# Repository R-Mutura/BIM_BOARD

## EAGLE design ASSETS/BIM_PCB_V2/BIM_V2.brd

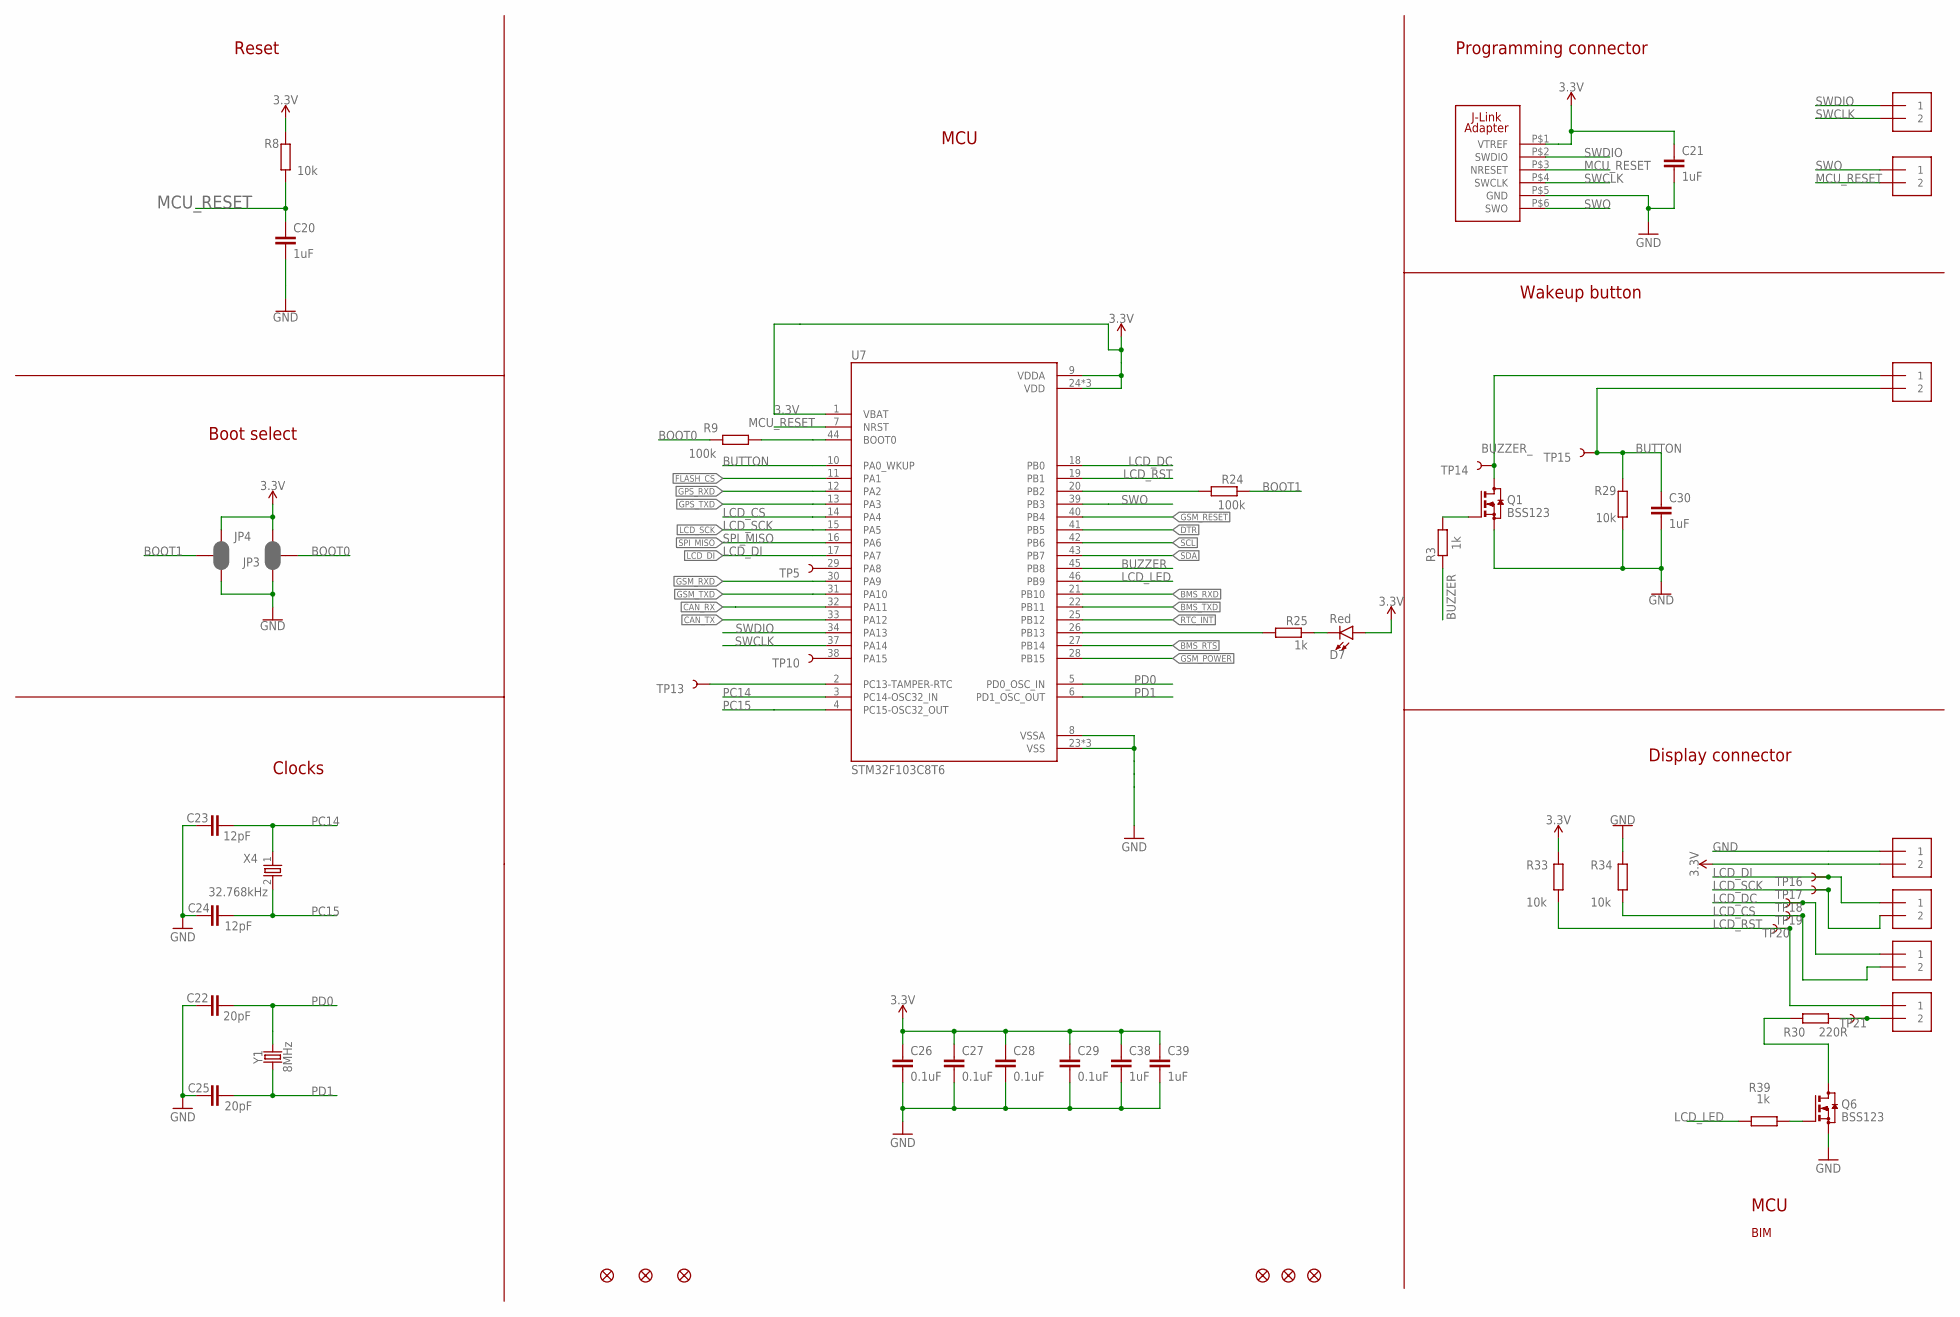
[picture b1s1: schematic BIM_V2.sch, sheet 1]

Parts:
C20, C21, C30, C38, C39: 1uF; C0402
C22, C25: 20pF; C0402
C23, C24: 12pF; C0402
C26, C27, C28, C29: 0.1uF; C0402
D7: Red; LED-0603
FD1, FD2, FD3, FD4, FD5, FD6: FIDUCIAL1X2; FIDUCIAL-1X2
JP3, JP4: JUMPER-SMT_3_2-NC_PASTE_SILK; SMT-JUMPER_3_2-NC_PASTE_SILK
Q1, Q6: BSS123; SOT23
R3, R25, R39: 1k; R0402
R8, R29, R33, R34: 10k; R0402
R9, R24: 100k; R0402
R30: 220R; R0402
S2, S3, S4: 1X2-3.5MM
TP5, TP10, TP13, TP14, TP15, TP16, TP17, TP18, TP19, TP20, TP21: TEST-POINT3X4; PAD.03X.04
U7: STM32F103C8T6; QFP50P900X900X160-48N
U$1: J-LINK_6-PIN_ADAPTER-1; J-LINK_6-PIN_ADAPTER_S
X3-1, X3-2, X3-3, X3-4: 1X2-3.5MM
X4: 32.768kHz; XTAL_3215_N
Y1: 8MHz; CRYSTAL-SMD-5X3.2-4PAD

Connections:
3.3V: C21.1, C26.1, C27.1, C28.1, C29.1, C38.1, C39.1, D7.A, JP3.3, JP4.3, R8.2, R33.1, U7.1 (VBAT), U7.9 (VDDA), U7.24 (VDD), U7.36 (VDD), U7.48 (VDD), U$1.P$1 (VTREF), X3-1.2; also elsewhere on the board
BMS_RTS: U7.27 (PB14); also elsewhere on the board
BMS_RXD: U7.21 (PB10); also elsewhere on the board
BMS_TXD: U7.22 (PB11); also elsewhere on the board
BOOT0: JP3.2, R9.2
BOOT1: JP4.2, R24.2
BUTTON: C30.1, R29.2, S2.2, TP15.P$1, U7.10 (PA0_WKUP)
BUZZER: R3.2, U7.45 (PB8)
BUZZER_: Q1.3 (D), S2.1, TP14.P$1
CAN_RX: U7.32 (PA11); also elsewhere on the board
CAN_TX: U7.33 (PA12); also elsewhere on the board
DTR: U7.41 (PB5); also elsewhere on the board
FLASH_CS: U7.11 (PA1); also elsewhere on the board
GND: C20.2, C21.2, C22.1, C23.1, C24.1, C25.1, C26.2, C27.2, C28.2, C29.2, C30.2, C38.2, C39.2, JP3.1, JP4.1, Q1.2 (S), Q6.2 (S), R29.1, R34.1, U7.8 (VSSA), U7.23 (VSS), U7.35 (VSS), U7.47 (VSS), U$1.P$5 (GND), X3-1.1; also elsewhere on the board
GPS_RXD: U7.12 (PA2); also elsewhere on the board
GPS_TXD: U7.13 (PA3); also elsewhere on the board
GSM_POWER: U7.28 (PB15); also elsewhere on the board
GSM_RESET: U7.40 (PB4); also elsewhere on the board
GSM_RXD: U7.30 (PA9); also elsewhere on the board
GSM_TXD: U7.31 (PA10); also elsewhere on the board
LCD_CS: R34.2, TP19.P$1, U7.14 (PA4), X3-3.2
LCD_DC: TP18.P$1, U7.18 (PB0), X3-3.1
LCD_DI: TP16.P$1, U7.17 (PA7), X3-2.1; also elsewhere on the board
LCD_LED: R39.2, U7.46 (PB9)
LCD_RST: R33.2, TP20.P$1, U7.19 (PB1), X3-4.1
LCD_SCK: TP17.P$1, U7.15 (PA5), X3-2.2; also elsewhere on the board
MCU_RESET: C20.1, R8.1, S4.2, U7.7 (NRST), U$1.P$3 (NRESET)
unnamed: TP5.P$1, U7.29 (PA8)
unnamed: Q1.1 (G), R3.1
unnamed: TP13.P$1, U7.2 (PC13-TAMPER-RTC)
unnamed: TP10.P$1, U7.38 (PA15)
unnamed: D7.C, R25.1
unnamed: R25.2, U7.26 (PB13)
unnamed: R9.1, U7.44 (BOOT0)
unnamed: R24.1, U7.20 (PB2)
unnamed: Q6.3 (D), R30.2
unnamed: R30.1, TP21.P$1, X3-4.2
unnamed: Q6.1 (G), R39.1
PC14: C23.2, U7.3 (PC14-OSC32_IN), X4.1
PC15: C24.2, U7.4 (PC15-OSC32_OUT), X4.2
PD0: C22.2, U7.5 (PD0_OSC_IN), Y1.3 (2)
PD1: C25.2, U7.6 (PD1_OSC_OUT), Y1.1
RTC_INT: U7.25 (PB12); also elsewhere on the board
SCL: U7.42 (PB6); also elsewhere on the board
SDA: U7.43 (PB7); also elsewhere on the board
SPI_MISO: U7.16 (PA6); also elsewhere on the board
SWCLK: S3.2, U7.37 (PA14), U$1.P$4 (SWCLK)
SWDIO: S3.1, U7.34 (PA13), U$1.P$2 (SWDIO)
SWO: S4.1, U7.39 (PB3), U$1.P$6 (SWO)

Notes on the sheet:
MCU
Reset
Boot select
Clocks
Programming connector
Wakeup button
Display connector
BIM

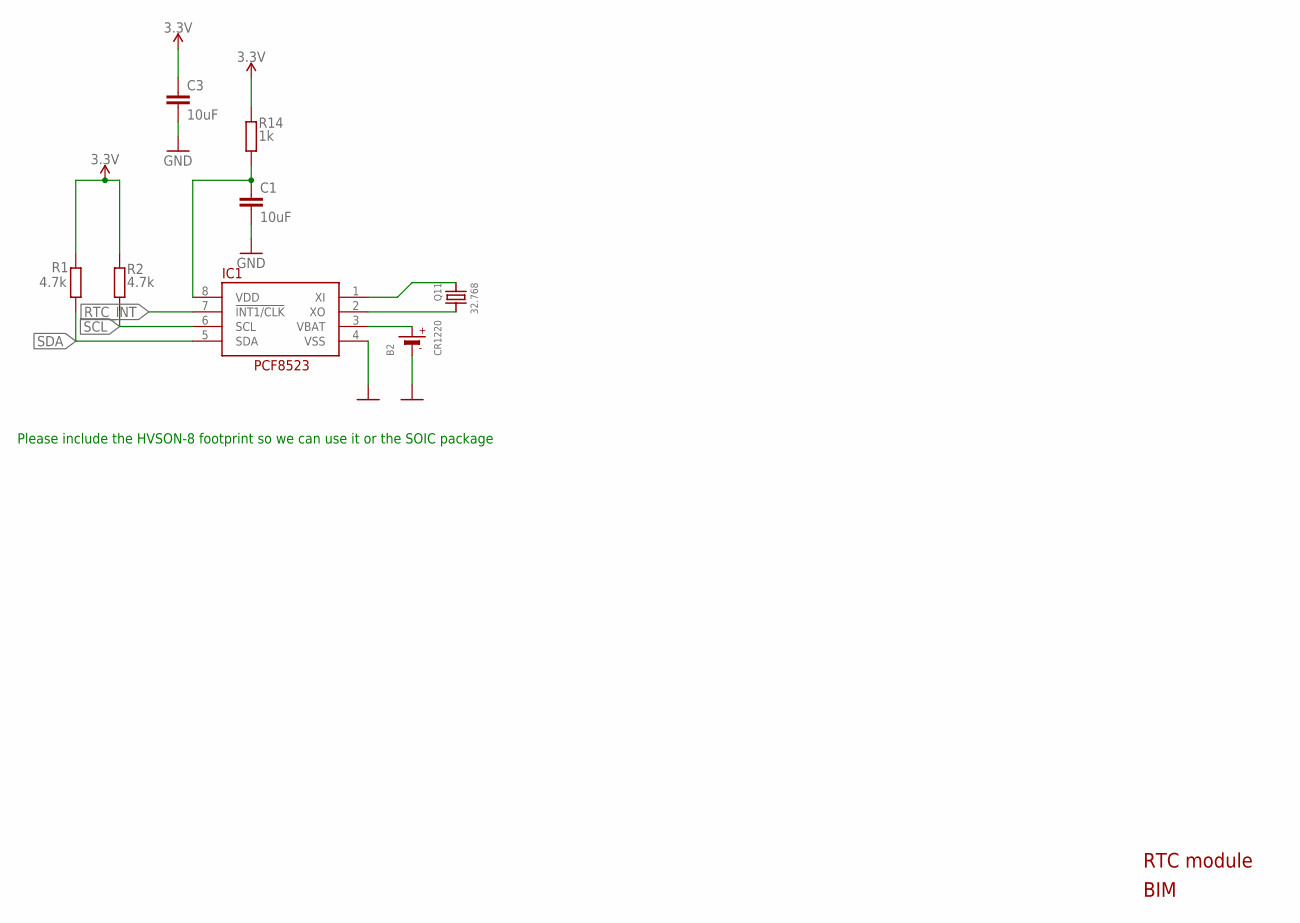
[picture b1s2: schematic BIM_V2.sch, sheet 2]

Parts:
B2: CR1220
C1, C3: 10uF; C0402
IC1: RTC_PCF8523T; SOIC8_150MIL
Q11: 32.768; CRYSTAL_8X3.8
R1, R2: 4.7k; R0402
R14: 1k; R0402

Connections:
3.3V: C3.1, R1.1, R2.1, R14.1; also elsewhere on the board
GND: B2.-, C1.2, C3.2, IC1.4 (VSS); also elsewhere on the board
unnamed: IC1.1 (XI), Q11.P$1 (1)
unnamed: IC1.2 (XO), Q11.P$4 (2)
unnamed: C1.1, IC1.8 (VDD), R14.2
RTC_INT: IC1.7 (!INT1/CLK); also elsewhere on the board
SCL: IC1.6 (SCL), R2.2; also elsewhere on the board
SDA: IC1.5 (SDA), R1.2; also elsewhere on the board
VBAT1: B2.+$1 (+), IC1.3 (VBAT)

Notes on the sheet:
RTC module
BIM
Please include the HVSON-8 footprint so we can use it or the SOIC package

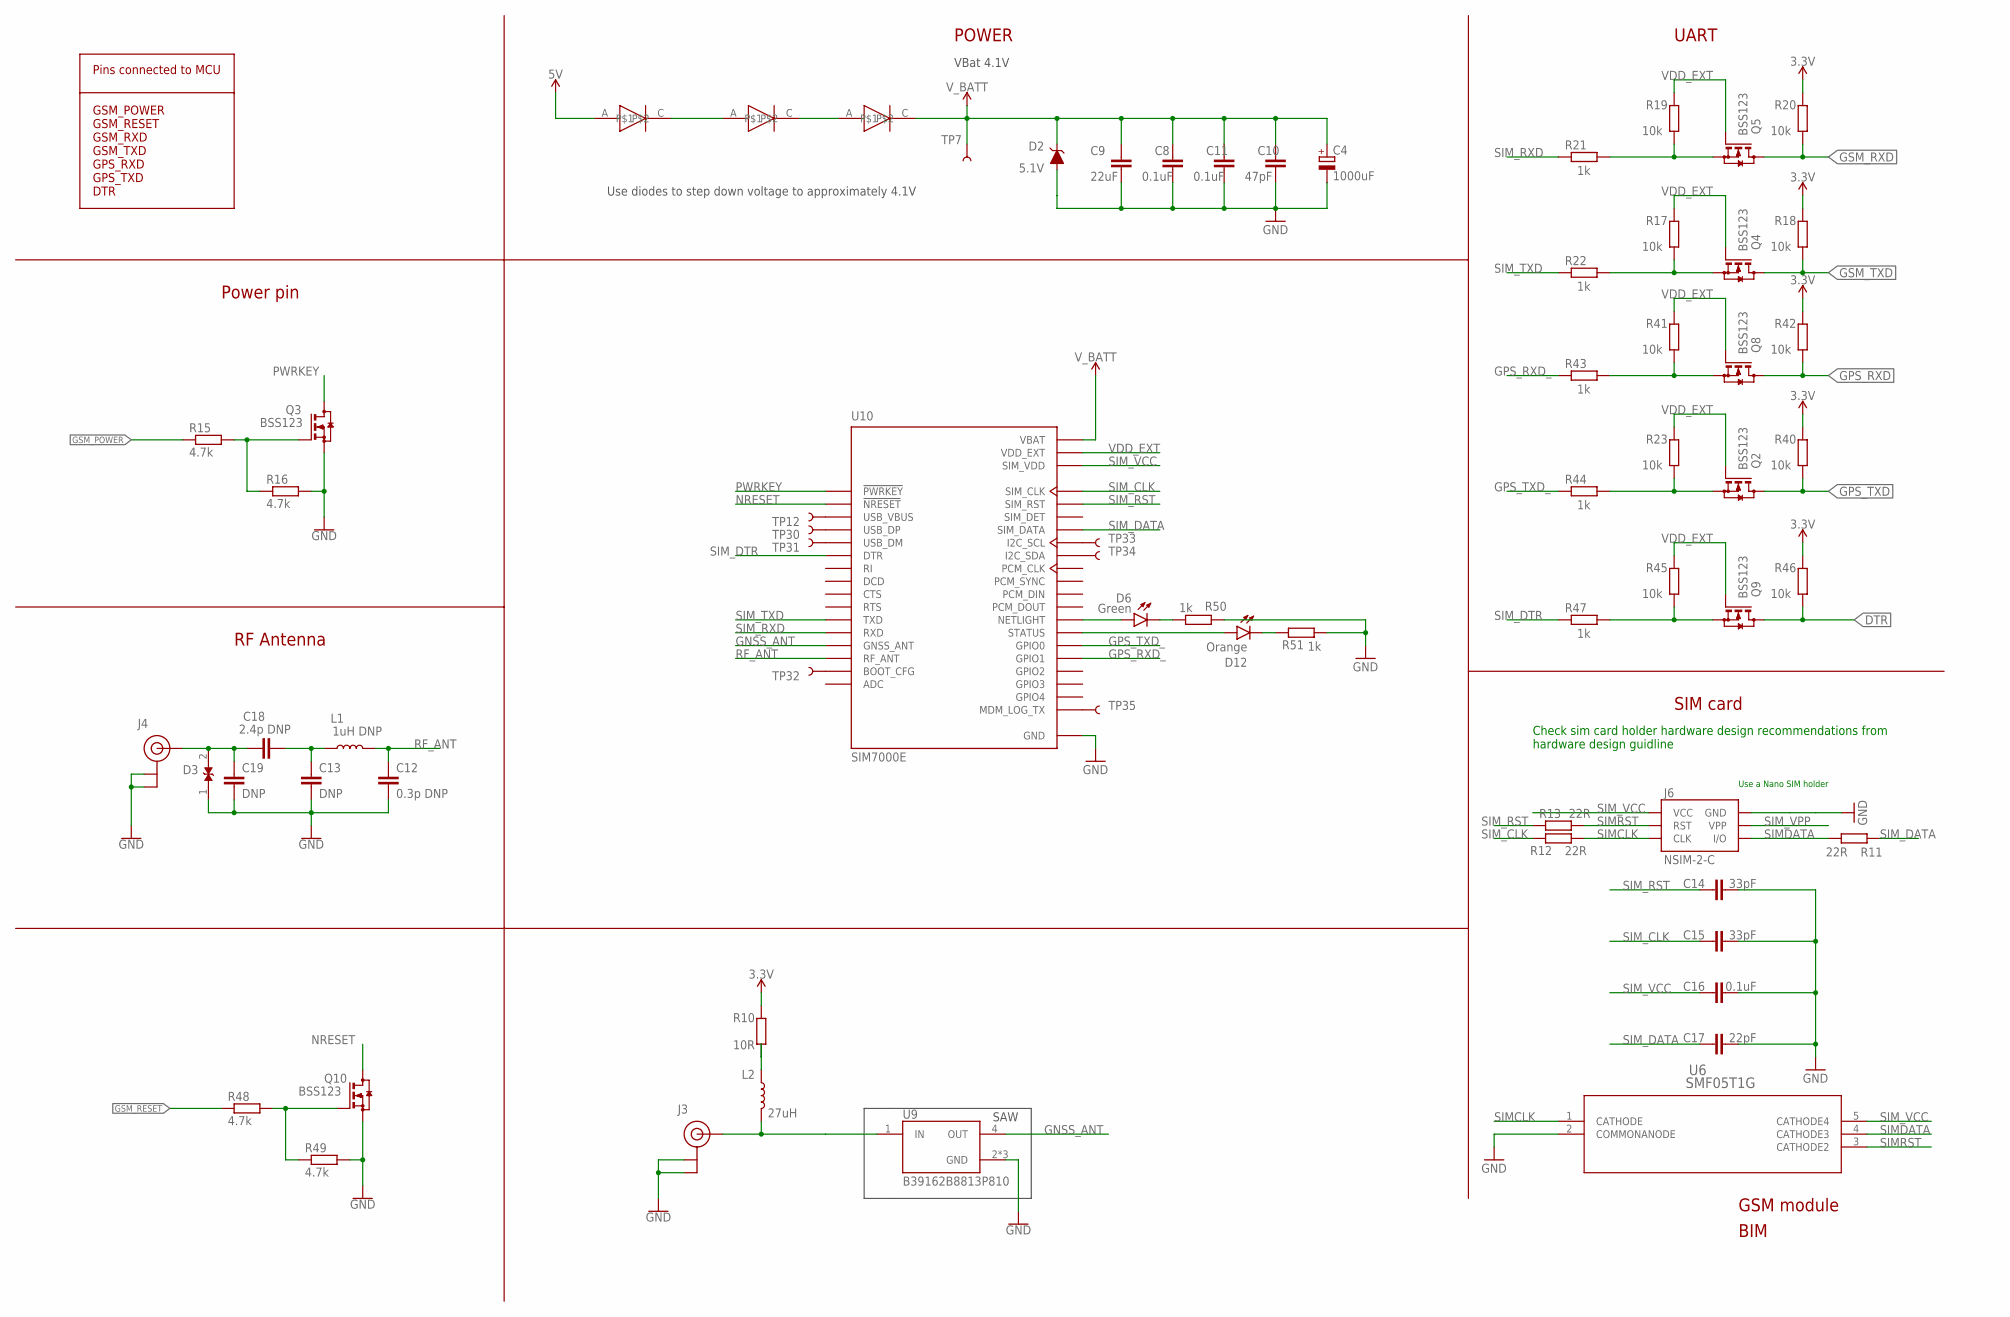
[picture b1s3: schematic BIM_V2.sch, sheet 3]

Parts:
C4: 1000uF; D/7343-31R
C8, C11, C16: 0.1uF; C0402
C9: 22uF; C0805
C10: 47pF; C0402
C12: 0.3p DNP; C0402
C13, C19: DNP; C0402
C14, C15: 33pF; C0402
C17: 22pF; C0402
C18: 2.4p DNP; C0402
D2: 5.1V; SOD-323
D3: D5V0L1B2LP4-7B; DIODFN100X60X40-2N
D6: Green; LED-0603
D12: Orange; LED-0603
J3, J4: U.FL
J6: NSIM-2-C; SIMHOLDER
L1: 1uH DNP; 0603
L2: 27uH; 0603
Q2, Q3, Q4, Q5, Q8, Q9, Q10: BSS123; SOT23
R10: 10R; R0402
R11, R12, R13: 22R; R0402
R15, R16, R48, R49: 4.7k; R0402
R17, R18, R19, R20, R23, R40, R41, R42, R45, R46: 10k; R0402
R21, R22, R43, R44, R47, R50, R51: 1k; R0402
TP7, TP12, TP30, TP31, TP32, TP33, TP34, TP35: TEST-POINT3X4; PAD.03X.04
U6: SMF05T1G; SC-88A-5_1P35X2P2_ONS
U9: B39162B8813P810; FIL_B39162B9417K610
U10: SIM7000E; SIMCON_SIM7000E
U$2, U$3: 0ohm 2010 resistor; DIOM5436X261N
U$4: HS3FB; DIOM5436X261N

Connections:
3.3V: R10.2, R18.2, R20.2, R40.2, R42.2, R46.2; also elsewhere on the board
5V: U$2.A; also elsewhere on the board
DTR: Q9.3 (D), R46.1; also elsewhere on the board
GND: C4.-, C8.2, C9.2, C10.2, C11.2, C12.2, C13.2, C14.2, C15.2, C16.2, C17.2, C19.2, D2.A, D3.1, J3.1 (GND), J3.2 (GND), J4.1 (GND), J4.2 (GND), J6.C5 (GND), Q3.2 (S), Q10.2 (S), R16.2, R49.2, R50.2, R51.2, U6.2 (COMMONANODE), U9.2 (GND), U9.3 (GND), U9.5 (GND), U10.2 (GND), U10.17 (GND), U10.18 (GND), U10.29 (GND), U10.39 (GND), U10.45 (GND), U10.46 (GND), U10.54 (GND), U10.58 (GND), U10.59 (GND), U10.61 (GND), U10.62 (GND), U10.63 (GND), U10.64 (GND), U10.65 (GND); also elsewhere on the board
GNSS_ANT: U9.4 (OUT), U10.53 (GNSS_ANT)
GPS_RXD: Q8.3 (D), R42.1; also elsewhere on the board
GPS_RXD_: R43.2, U10.49 (GPIO1)
GPS_TXD: Q2.3 (D), R40.1; also elsewhere on the board
GPS_TXD_: R44.2, U10.50 (GPIO0)
GSM_POWER: R15.1; also elsewhere on the board
GSM_RESET: R48.1; also elsewhere on the board
GSM_RXD: Q5.3 (D), R20.1; also elsewhere on the board
GSM_TXD: Q4.3 (D), R18.1; also elsewhere on the board
unnamed: Q10.1 (G), R48.2, R49.1
unnamed: Q3.1 (G), R15.2, R16.1
unnamed: U$3.C, U$4.A
unnamed: U$2.C, U$3.A
unnamed: C13.1, C18.2, L1.1
unnamed: J3.FEED (SIGNAL), L2.2, U9.1 (IN)
unnamed: TP33.P$1, U10.38 (I2C_SCL)
unnamed: L2.1, R10.1
unnamed: TP12.P$1, U10.24 (USB_VBUS)
unnamed: TP30.P$1, U10.27 (USB_DP)
unnamed: TP31.P$1, U10.28 (USB_DM)
unnamed: TP34.P$1, U10.37 (I2C_SDA)
unnamed: D6.C, R50.1
unnamed: D6.A, U10.52 (NETLIGHT)
unnamed: D12.C, R51.1
unnamed: D12.A, U10.66 (STATUS)
unnamed: TP32.P$1, U10.6 (BOOT_CFG)
unnamed: TP35.P$1, U10.23 (MDM_LOG_TX)
NRESET: Q10.3 (D), U10.16 (!NRESET)
PWRKEY: Q3.3 (D), U10.1 (!PWRKEY)
RF_ANT: C12.1, C18.1, C19.1, D3.2, J4.FEED (SIGNAL), L1.2, U10.60 (RF_ANT)
SIMCLK: J6.C3 (CLK), R12.2, U6.1 (CATHODE)
SIMDATA: J6.C7 (I/O), R11.2, U6.4 (CATHODE3)
SIMRST: J6.C2 (RST), R13.2, U6.3 (CATHODE2)
SIMRXD: Q5.2 (S), R19.1, R21.1
SIMRXD1: Q8.2 (S), R41.1, R43.1
SIMTXD: Q4.2 (S), R17.1, R22.1
SIMTXD1: Q2.2 (S), R23.1, R44.1
SIMTXD2: Q9.2 (S), R45.1, R47.1
SIM_CLK: C15.1, R12.1, U10.32 (SIM_CLK)
SIM_DATA: C17.1, R11.1, U10.31 (SIM_DATA)
SIM_DTR: R47.2, U10.3 (DTR)
SIM_RST: C14.1, R13.1, U10.33 (SIM_RST)
SIM_RXD: R21.2, U10.10 (RXD)
SIM_TXD: R22.2, U10.9 (TXD)
SIM_VCC: C16.1, J6.C1 (VCC), U6.5 (CATHODE4), U10.30 (SIM_VDD)
SIM_VPP: J6.C6 (VPP)
VDD_EXT: Q2.1 (G), Q4.1 (G), Q5.1 (G), Q8.1 (G), Q9.1 (G), R17.2, R19.2, R23.2, R41.2, R45.2, U10.15 (VDD_EXT)
V_BATT: C4.+, C8.1, C9.1, C10.1, C11.1, D2.C, TP7.P$1, U10.55 (VBAT), U10.56 (VBAT), U10.57 (VBAT), U$4.C

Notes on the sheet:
GSM module
VBat 4.1V
Check sim card holder hardware design recommendations from hardware design guidline
Pins connected to MCU GSM_POWER GSM_RESET GSM_RXD GSM_TXD GPS_RXD GPS_TXD DTR
UART
SIM card
POWER
Use diodes to step down voltage to approximately 4.1V
RF Antenna
Power pin
BIM
SAW
Use a Nano SIM holder

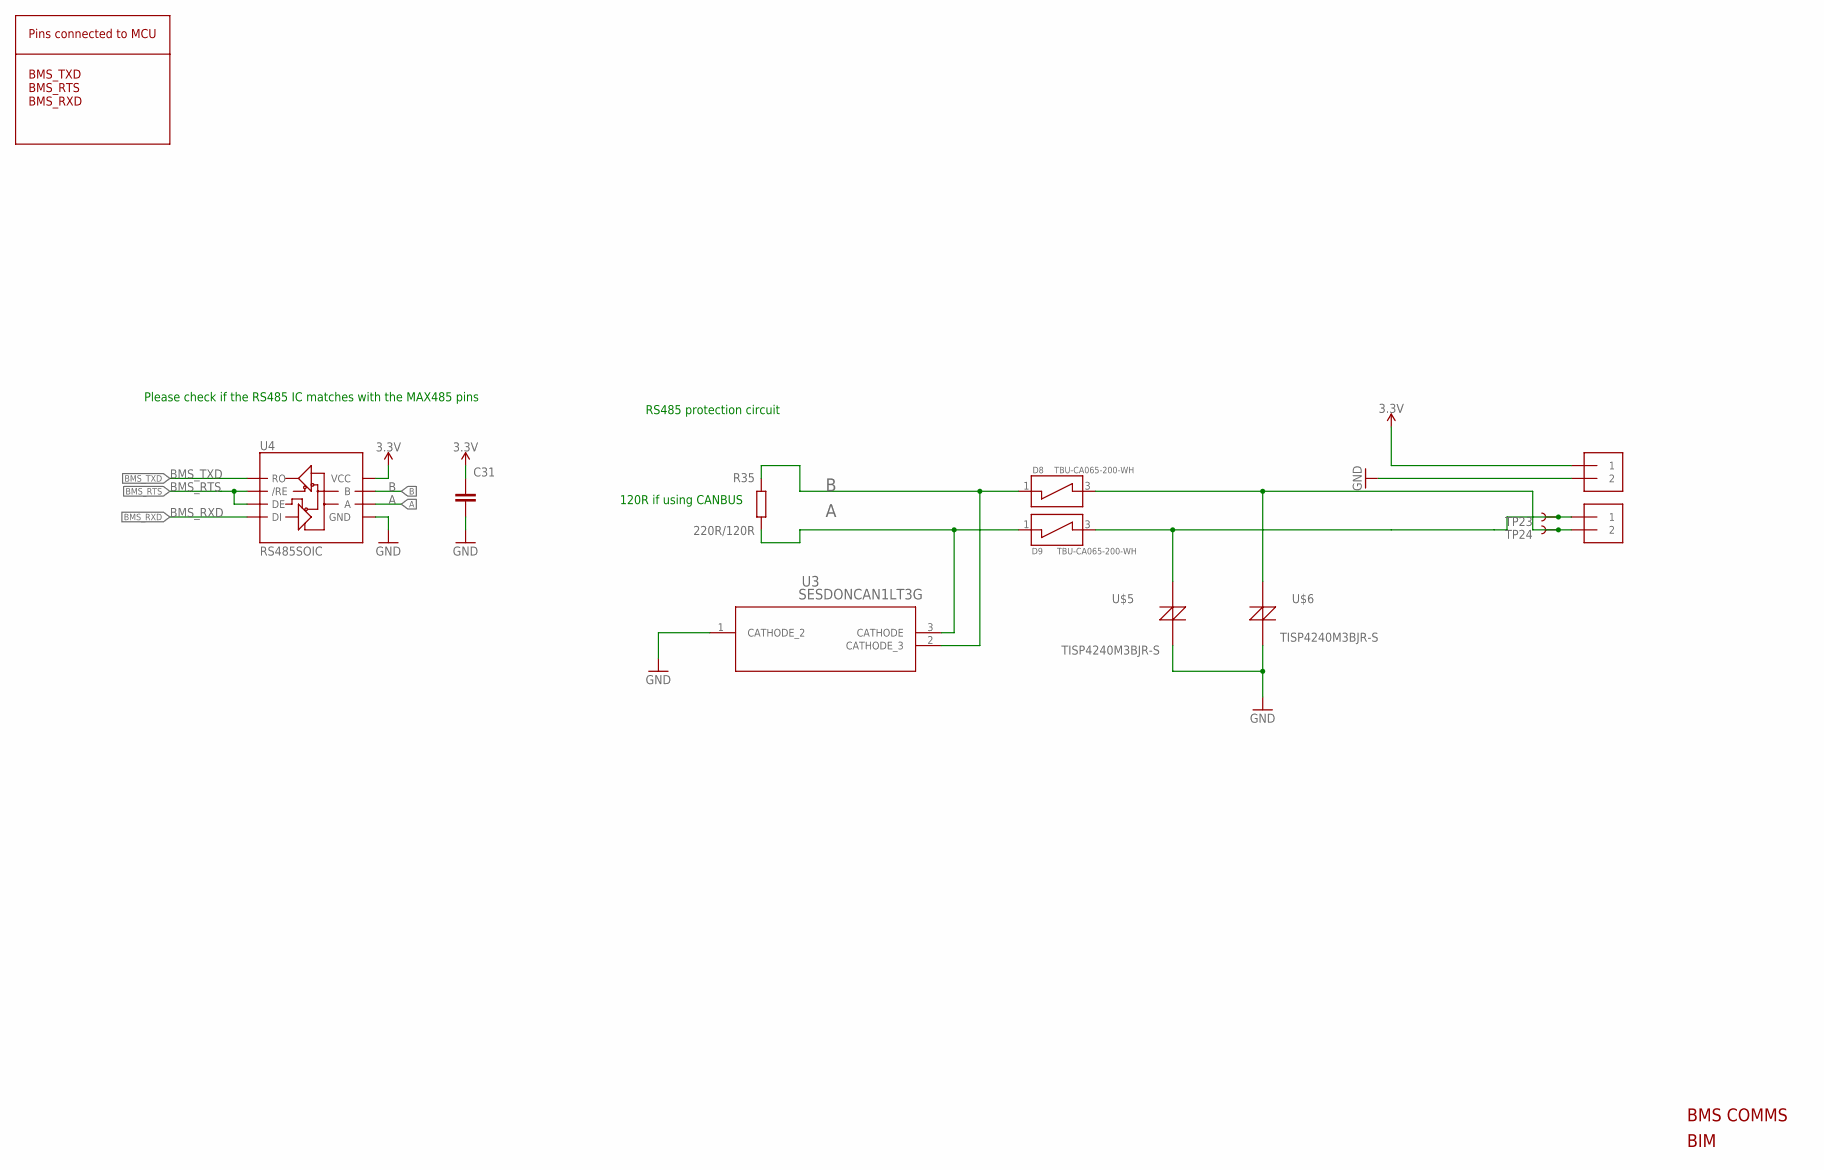
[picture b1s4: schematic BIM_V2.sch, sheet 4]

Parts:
C31: 0.1uF; C0402
D8, D9: TBU-CA065-200-WH; DIOC650X400X100N
R35: 220R/120R; R0402
TP23, TP24: TEST-POINT3X4; PAD.03X.04
U3: SESDONCAN1LT3G; SOT-23_ONS
U4: RS485SOIC; SO08
U$5, U$6: TISP4240M3BJR-S; DO-214AA
X1-1, X1-2: 1X2-3.5MM

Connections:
3.3V: C31.1, U4.8 (VCC), X1-1.1; also elsewhere on the board
A: D9.1, R35.1, U3.3 (CATHODE), U4.6 (A); also elsewhere on the board
B: D8.1, R35.2, U3.2 (CATHODE_3), U4.7 (B); also elsewhere on the board
BMS_RTS: U4.2 (/RE), U4.3 (DE); also elsewhere on the board
BMS_RXD: U4.4 (DI); also elsewhere on the board
BMS_TXD: U4.1 (RO); also elsewhere on the board
GND: C31.2, U3.1 (CATHODE_2), U4.5 (GND), U$5.1, U$6.1, X1-1.2; also elsewhere on the board
unnamed: D9.3, TP23.P$1, U$5.2, X1-2.1
unnamed: D8.3, TP24.P$1, U$6.2, X1-2.2

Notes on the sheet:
BMS COMMS
Pins connected to MCU BMS_TXD BMS_RTS BMS_RXD
Please check if the RS485 IC matches with the MAX485 pins
RS485 protection circuit
BIM
120R if using CANBUS

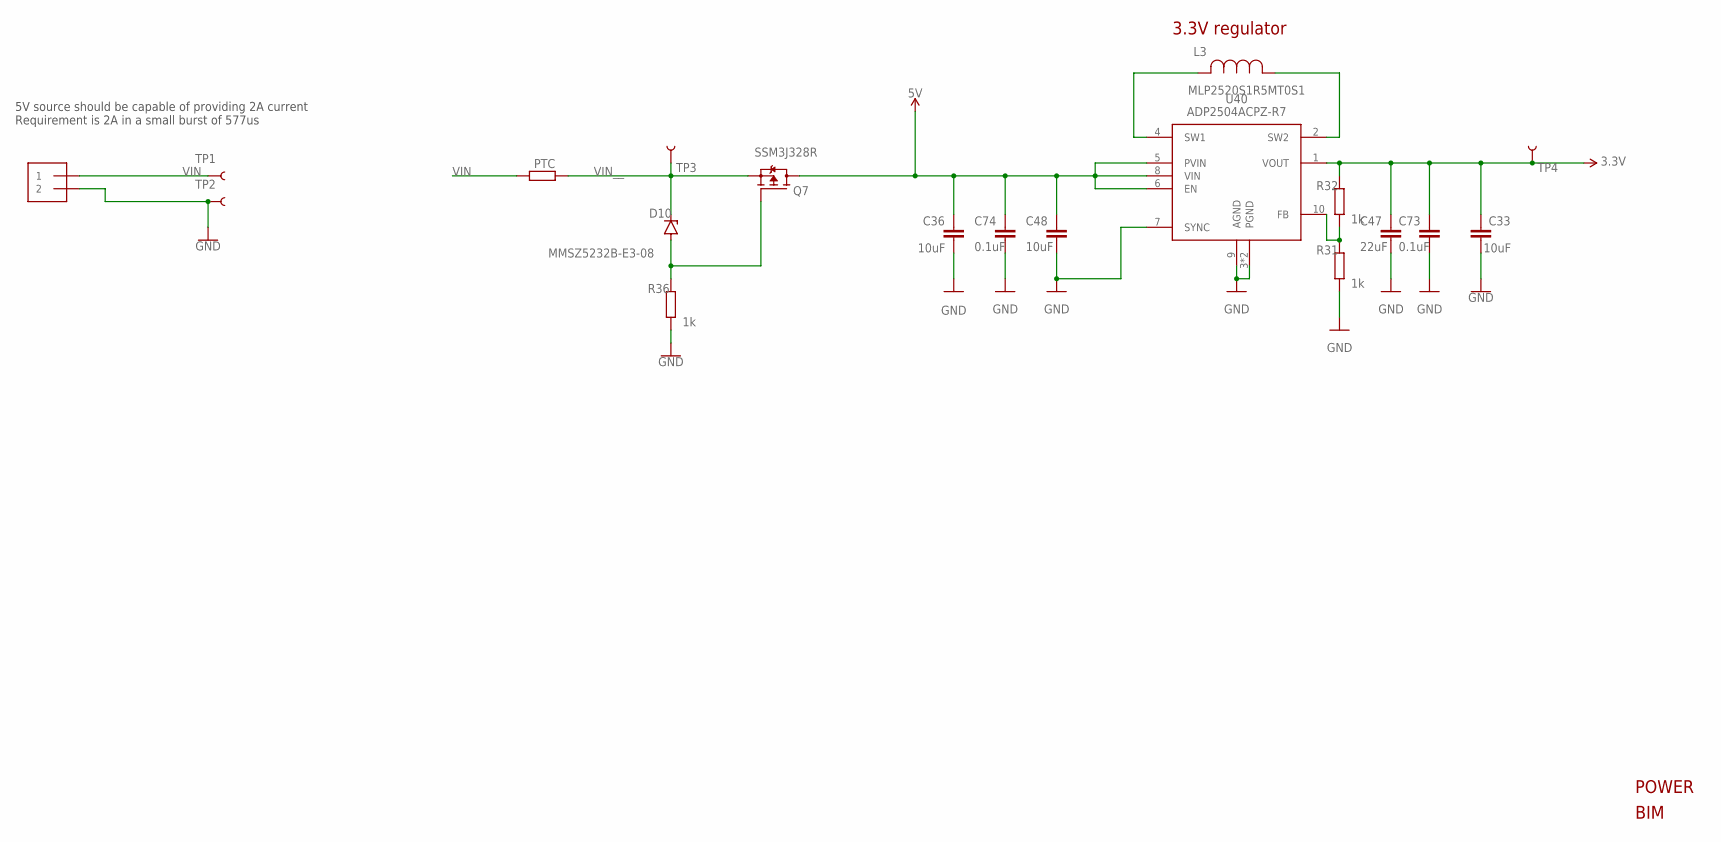
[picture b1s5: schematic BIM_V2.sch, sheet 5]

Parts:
C33, C36: 10uF; C0603
C47: 22uF; C0603
C48: 10uF; C0402
C73, C74: 0.1uF; C0402
D10: MMSZ5232B-E3-08; SOD80C
L3: MLP2520S1R5MT0S1; IND_2520_TDK
PTC: PRG18BC1R0MM1RB; R0603
Q7: SSM3J328R; SOT-23F
R31, R32, R36: 1k; R0402
TP1, TP2, TP3, TP4: TEST-POINT3X4; PAD.03X.04
U40: ADP2504ACPZ-R7; SON50P300X300X80-11N
X2: 1X2-3.5MM

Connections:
3.3V: C33.1, C47.1, C73.1, R32.1, TP4.P$1, U40.1 (VOUT); also elsewhere on the board
5V: C36.1, C48.1, C74.1, Q7.3 (D), U40.5 (PVIN), U40.6 (EN), U40.8 (VIN); also elsewhere on the board
GND: C33.2, C36.2, C47.2, C48.2, C73.2, C74.2, R31.2, R36.2, TP2.P$1, U40.3 (PGND), U40.7 (SYNC), U40.9 (AGND), U40.11 (PGND), X2.2; also elsewhere on the board
unnamed: R31.1, R32.2, U40.10 (FB)
unnamed: D10.A, Q7.1 (G), R36.1
unnamed: L3.2, U40.4 (SW1)
unnamed: L3.1, U40.2 (SW2)
VIN: PTC.2, TP1.P$1, X2.1
VIN__: D10.C, PTC.1, Q7.2 (S), TP3.P$1

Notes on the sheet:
POWER
5V source should be capable of providing 2A current Requirement is 2A in a small burst of 577us
BIM
3.3V regulator

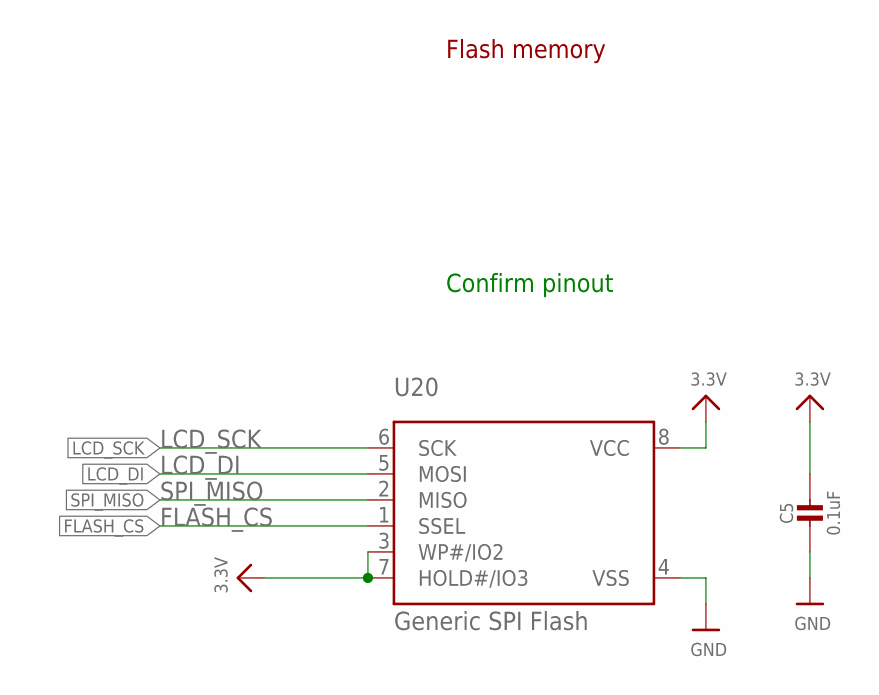
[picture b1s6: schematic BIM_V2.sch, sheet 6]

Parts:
C5: 0.1uF; 0603-NO
U20: Generic SPI Flash; SOIC8_208MIL

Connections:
3.3V: C5.1, U20.3 (WP#/IO2), U20.7 (HOLD#/IO3), U20.8 (VCC); also elsewhere on the board
FLASH_CS: U20.1 (SSEL); also elsewhere on the board
GND: C5.2, U20.4 (VSS); also elsewhere on the board
LCD_DI: U20.5 (MOSI); also elsewhere on the board
LCD_SCK: U20.6 (SCK); also elsewhere on the board
SPI_MISO: U20.2 (MISO); also elsewhere on the board

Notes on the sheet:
Flash memory
Confirm pinout

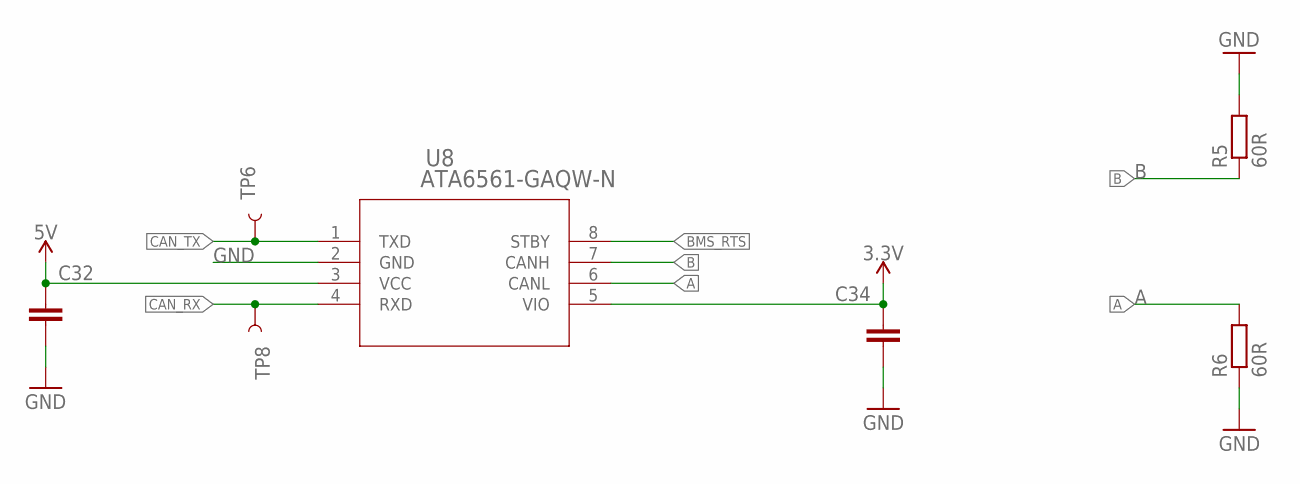
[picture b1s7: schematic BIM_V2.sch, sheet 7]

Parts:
C32, C34: 0.1uF; C0402
R5, R6: 60R; R0402
TP6, TP8: TEST-POINT3X4; PAD.03X.04
U8: ATA6561-GAQW-N; SOIC8_4P9X3P9MC_MCH

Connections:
3.3V: C34.1, U8.5 (VIO); also elsewhere on the board
5V: C32.1, U8.3 (VCC); also elsewhere on the board
A: R6.2, U8.6 (CANL); also elsewhere on the board
B: R5.1, U8.7 (CANH); also elsewhere on the board
BMS_RTS: U8.8 (STBY); also elsewhere on the board
CAN_RX: U8.4 (RXD); also elsewhere on the board
CAN_TX: U8.1 (TXD); also elsewhere on the board
GND: C32.2, C34.2, R5.2, R6.1, U8.2 (GND); also elsewhere on the board

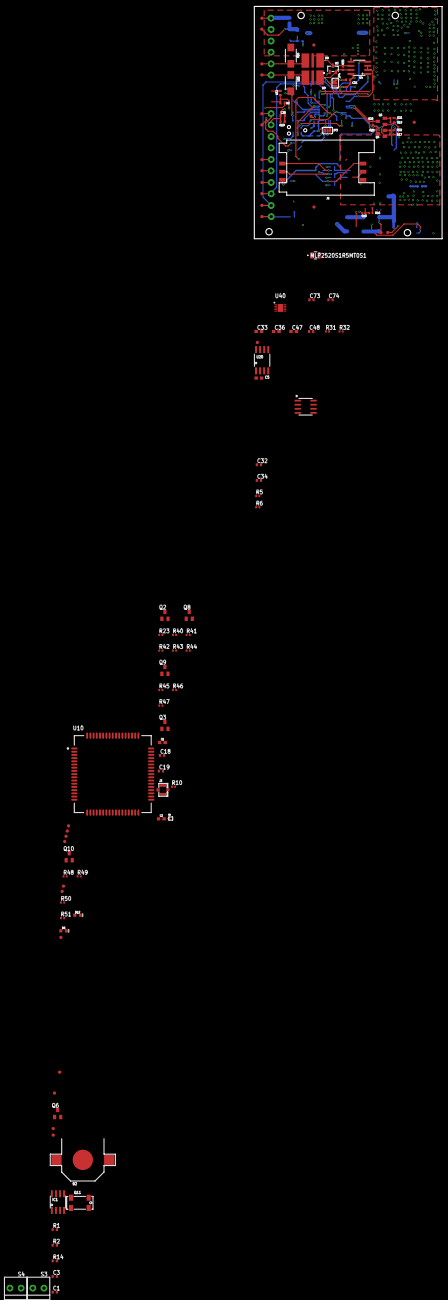
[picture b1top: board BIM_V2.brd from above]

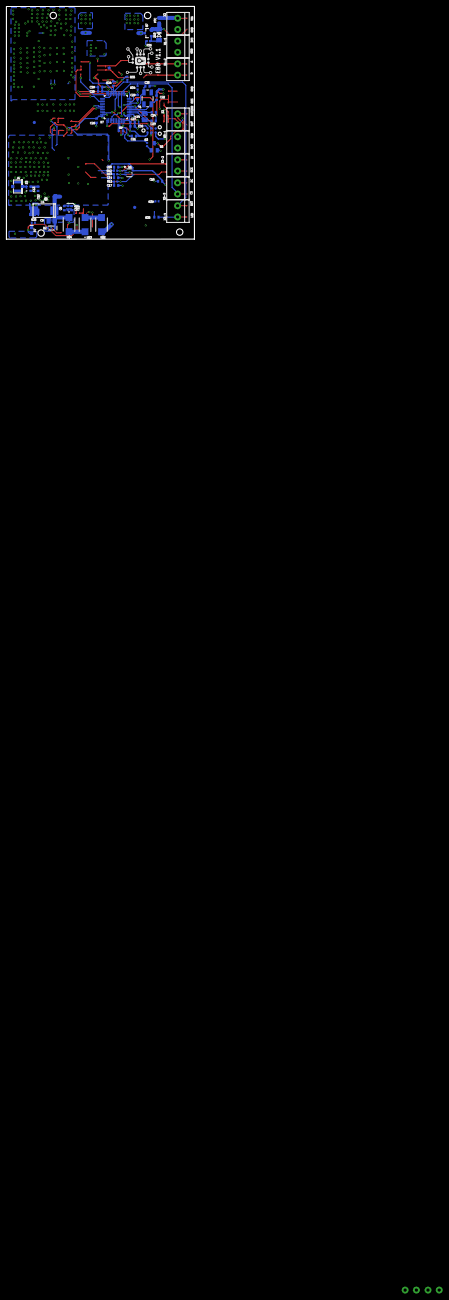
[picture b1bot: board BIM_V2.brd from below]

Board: 4 copper layers, 58.6 x 72.5 mm, 172 parts (61 on the bottom side), 105 nets.

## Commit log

2023-12-07 updates on schematic and complete layout
2023-12-10 completed design PCN and Images
2023-12-11 complete BIM Board
2023-12-12 small updates
2023-12-12 updates on the buck 3v3 supply
2023-12-12 bom updates
2023-12-17 update to A9G and connector
2023-12-18 updated step
2023-12-18 updated GENERAL
2023-12-21 xmas
2024-01-13 completed gerber and placement
2024-01-16 updates in BOM gerber and PCL
2024-01-16 completed project
2024-01-17 completed BIM board- ECOBoda
2024-01-23 completed project and all the prouction files
2024-01-28 all items updated
2024-01-28 all items updated including fiducial
2024-02-07 BIM updated BOM and placement files guide pdf added

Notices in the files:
parts and their libraries:
SparkFun-LED: Licensing: Creative Commons ShareAlike 4.0 International - https://creativecommons.org/licenses/by-sa/4.0
microbuilder: This work is placed in the public domain, and may be freely used for commercial and non-commercial work with the following conditions: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
